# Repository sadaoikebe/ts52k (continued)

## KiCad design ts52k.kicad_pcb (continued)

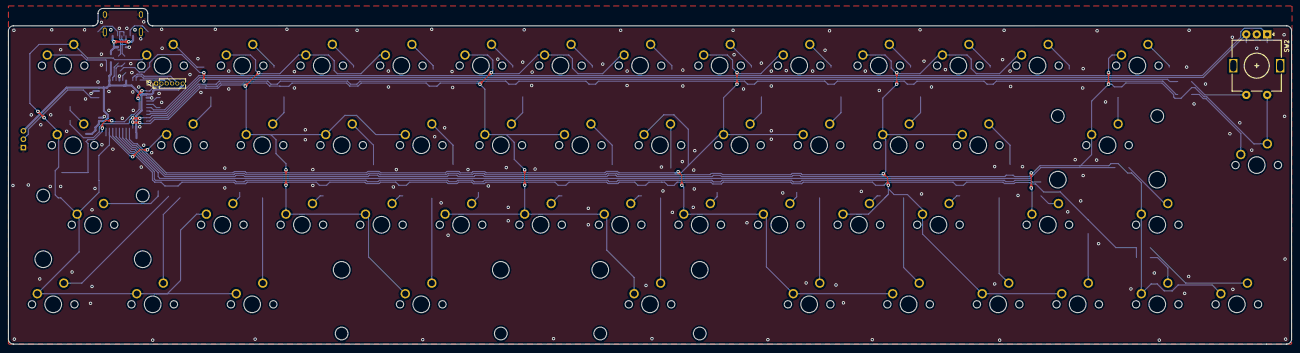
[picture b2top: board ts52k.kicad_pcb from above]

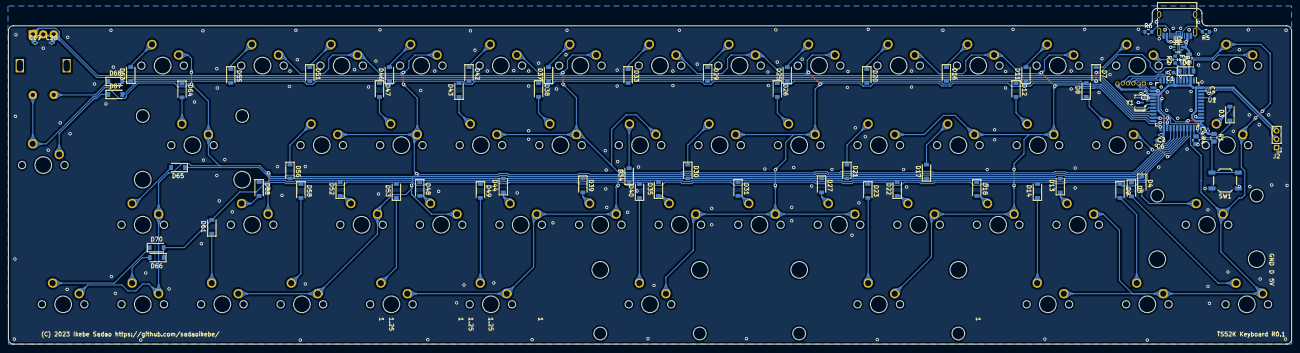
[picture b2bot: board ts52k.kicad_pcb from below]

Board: 2 copper layers, 307.2 x 80.4 mm, 128 parts (74 on the bottom side), 84 nets.

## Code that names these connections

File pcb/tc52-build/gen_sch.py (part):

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                 fp=R0402, lcsc='C25741', mpn='0402WGF1003TCE')
    # --- row series resistors ----------------------------------------------
    yr = 182.88
    sh.text('Row drive: GPIO21..18 -> 100R -> ROW1..4 (ROW1 = GPIO21)', 25.4, yr - 12.7, 2.5)
    for ri in range(1, 5):
        sh.place('Device:R', f'R{30+ri}', '100', 40.64 + (ri - 1) * 30.48, yr, {'1': f'ROW{ri}_DRV', '2': f'ROW{ri}'},
                 fp=R0402, lcsc='C25076', mpn='0402WGF1000TCE')
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

# ---------------------------------------------------------------- root + rp2040
GPIO_NETS = [(0, 'ENC_B'), (1, 'ENC_A'), (2, 'ENC_SW'), (18, 'ROW4_DRV'), (19, 'ROW3_DRV'), (20, 'ROW2_DRV'),
             (21, 'ROW1_DRV'), (3, 'S3B'), (4, 'S2B'), (5, 'S1B'), (7, 'INHB'), (8, 'S3A'), (9, 'S2A'), (10, 'S1A'), (11, 'INHA'), (26, 'ADC'), (28, 'SENSE')]


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    new = []
    for i, (g, net) in enumerate(GPIO_NETS):
        new.append(glabel(net, 106.68, 44.45 + 2.54 * i, 0, 'bidirectional'))
    # encoder push switch: S1 -> ENC_SW (GPIO2, internal pull-up), S2 -> GND
    new.append(glabel('ENC_SW', 247.65, 64.77, 180))
    new.append(glabel('GND', 247.65, 59.69, 180))
    new.append(['sheet', ['at', '152.4', '60.96'], ['size', '71.12', '40.64'], ['exclude_from_sim', 'no'], ['in_bom', 'yes'],
                ['on_board', 'yes'], ['dnp', 'no'], ['stroke', ['width', '0.1524'], ['type', 'solid']],
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                ['property', Q('Sheetfile'), Q('ec.kicad_sch'), ['at', '152.4', '102.3', '0'],
                 ['effects', ['font', ['size', '1.27', '1.27']], ['justify', 'left', 'top']]],
                ['instances', ['project', Q('ts52k'), ['path', Q('/' + ROOT_UUID), ['page', Q('3')]]]]])
    new.append(['text', Q('TC52: capacitive matrix (52 electrodes), column MUX x2 and analog front end\\nare on sheet ec. Nets are joined by global labels:\\nROW1..4_DRV, INHA/S1A..S3A, INHB/S1B..S3B, SENSE (purge, GPIO28), ADC (GPIO26 = ADC0), ENC_SW'),
                ['exclude_from_sim', 'no'], ['at', '154.94', '82.0', '0'],
                ['effects', ['font', ['size', '1.6', '1.6']], ['justify', 'left']], ['uuid', Q(uid('root-note'))]])
    out[idx:idx] = new
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
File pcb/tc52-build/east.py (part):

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        ('S1B', 73.3), ('PB', 73.825), ('INHB', 74.35), ('PA', 74.875), ('S3A', 75.4), ('S2A', 75.7), ('S1A', 76.0), ('INHA', 76.3)]
NET = {'BOOT': 'Net-(R14-Pad2)', 'PB': '+3V3M', 'PA': '+3V3M'}
XG0 = 38.75
PIN = {'ENC_B': 2, 'ENC_A': 3, 'ENC_SW': 4, 'S3B': 5, 'S2B': 6, 'S1B': 7, 'INHB': 9, 'S3A': 11, 'S2A': 12, 'S1A': 13, 'INHA': 14}
CA = {'ENC_B': 31.57, 'ENC_A': 31.994, 'ENC_SW': 32.418, 'S3B': 32.842, 'S2B': 33.266, 'S1B': 33.69, 'PB': 34.432,
      'INHB': 35.175, 'PA': 35.92}
XQ = {'+3V3': 36.0, 'ENC_B': 35.7, 'ENC_A': 35.4, 'ENC_SW': 35.1, 'S3B': 34.8, 'S2B': 34.5, 'S1B': 34.2, 'PB': 33.85,
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
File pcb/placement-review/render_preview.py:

"""Render the KiCad SVG export, with readable labels on the rough-placement view.

Uses PyMuPDF from the existing temporary PDF-tools directory. This draws no PCB
geometry; rough.svg is exported directly from ts52k.kicad_pcb by kicad-cli.
"""
from pathlib import Path
import os
import sys
import xml.etree.ElementTree as ET

sys.path.insert(0, os.path.join(os.environ['TEMP'], 'ts52k-pdf-tools'))
import pymupdf

OUT = Path(__file__).resolve().parent
svg = ET.parse(OUT / 'rough.svg').getroot()
ns = '{http://www.w3.org/2000/svg}'
def label(x,y,text,size=1.1):
    ET.SubElement(svg, ns+'rect', {'x':str(x-.25),'y':str(y-size),
        'width':str(len(text)*size*.62+.5),'height':str(size*1.3),
        'fill':'white','fill-opacity':'.94'})
    node = ET.SubElement(svg, ns+'text', {'x':str(x),'y':str(y),
        'font-family':'sans-serif','font-size':str(size),'font-weight':'bold',
        'fill':'#101820','stroke':'none'})
    node.text = text

label(2.0,55.0,'MATRIX JOINS / 2026-11-08',1.25)
label(2.0,57.0,'column lanes revised; col4 / col2 / col1 joined; 13 remain',.85)
annotated=ET.tostring(svg,encoding='utf-8',xml_declaration=True)
doc=pymupdf.open(stream=annotated,filetype='svg')
pdf=pymupdf.open('pdf',doc.convert_to_pdf())
page=pdf[0]
page.get_pixmap(matrix=pymupdf.Matrix(3,3)).save(OUT/'overview.png')
crop=pymupdf.Rect(0,0,67*72/25.4,60*72/25.4)
page.get_pixmap(matrix=pymupdf.Matrix(6,6),clip=crop).save(OUT/'mcu-area.png')
print('Rendered overview.png and mcu-area.png from actual PCB SVG')

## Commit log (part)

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2023-07-03 change to QFN
2023-07-04 jlcpcb ordered
2023-07-05 add case
2023-07-05 add plate
2023-07-07 widen the stabilizer holes as they are too tight
2023-07-07 adjust tabs then add dxf
2023-07-13 add brim
2023-07-13 chamfer lid for flipped printing
2023-07-18 tighter fit
2023-07-18 base fill
2023-10-20 case v1 release
2023-10-20 slimmer case
2024-12-08 add readme
2024-12-08 add bom
2024-12-10 add foot
2025-01-21 update lid 3mf
2026-02-23 plate - lthumb with 2u stabilizer
2026-02-23 add footprint for 275/225 spacebar
2026-04-17 rp2040 sym
2026-05-09 Update case geometry 2026
2026-05-09 add flash circuitry
2026-05-09 labels
2026-05-09 gpio wiring
2026-05-09 circuitry
2026-05-10 tag connect tc2030
